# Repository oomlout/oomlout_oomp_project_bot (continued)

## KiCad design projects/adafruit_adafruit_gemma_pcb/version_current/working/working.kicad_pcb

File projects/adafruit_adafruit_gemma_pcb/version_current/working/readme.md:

# OOMP Project  
## Adafruit-Gemma-PCB  by adafruit  
  
oomp key: oomp_projects_flat_adafruit_adafruit_gemma_pcb  
(snippet of original readme)  
  
-- Adafruit Gemma Classic (ATtiny85) PCB  
<a href="http://www.adafruit.com/products/1222"><br/>  
Click here to purchase one from the Adafruit shop</a>  
  
Deprecation Warning: The Gemma bit-bang USB technique it uses doesn't work as well as it did in 2014, many modern computers won't work well. So while we still carry the Gemma so that people can maintain some older projects, we no longer recommend it. Please check out the Gemma M0. It has built-in USB, more capabilities, and is comparable in price!  
  
GEMMA is a tiny wearable platform board with a lot of might in a 1" diameter package. Powered by a Attiny85 and programmable with an Arduino IDE over USB, you'll be able to realize any wearable project!  
  
We wanted to design a microcontroller board that was small enough to fit into any project, and low cost enough to use without hesitation. Perfect for when you don't want to give up your Flora and you aren't willing to take apart the project you worked so hard to design. It's our lowest-cost sewable controller!  
  
The Attiny85 is a fun processor because despite being so small, it has 8K of flash, and 5 I/O pins, including analog inputs and PWM 'analog' outputs. We designed a USB bootloader so you can plug it into any computer and reprogram it over a USB port just like an Arduino (it uses 2 of the 5 I/O pins, leaving you with 3). In fact we even made some simple modifications to the Arduino IDE so that it works like a mini-Flora. Perfect   
  full source readme at [readme_src.md](readme_src.md)  
  
source repo at: [https://github.com/adafruit/Adafruit-Gemma-PCB](https://github.com/adafruit/Adafruit-Gemma-PCB)  
## Board  

## Schematic  

[schematic pdf](working_schematic.pdf)  
## Images

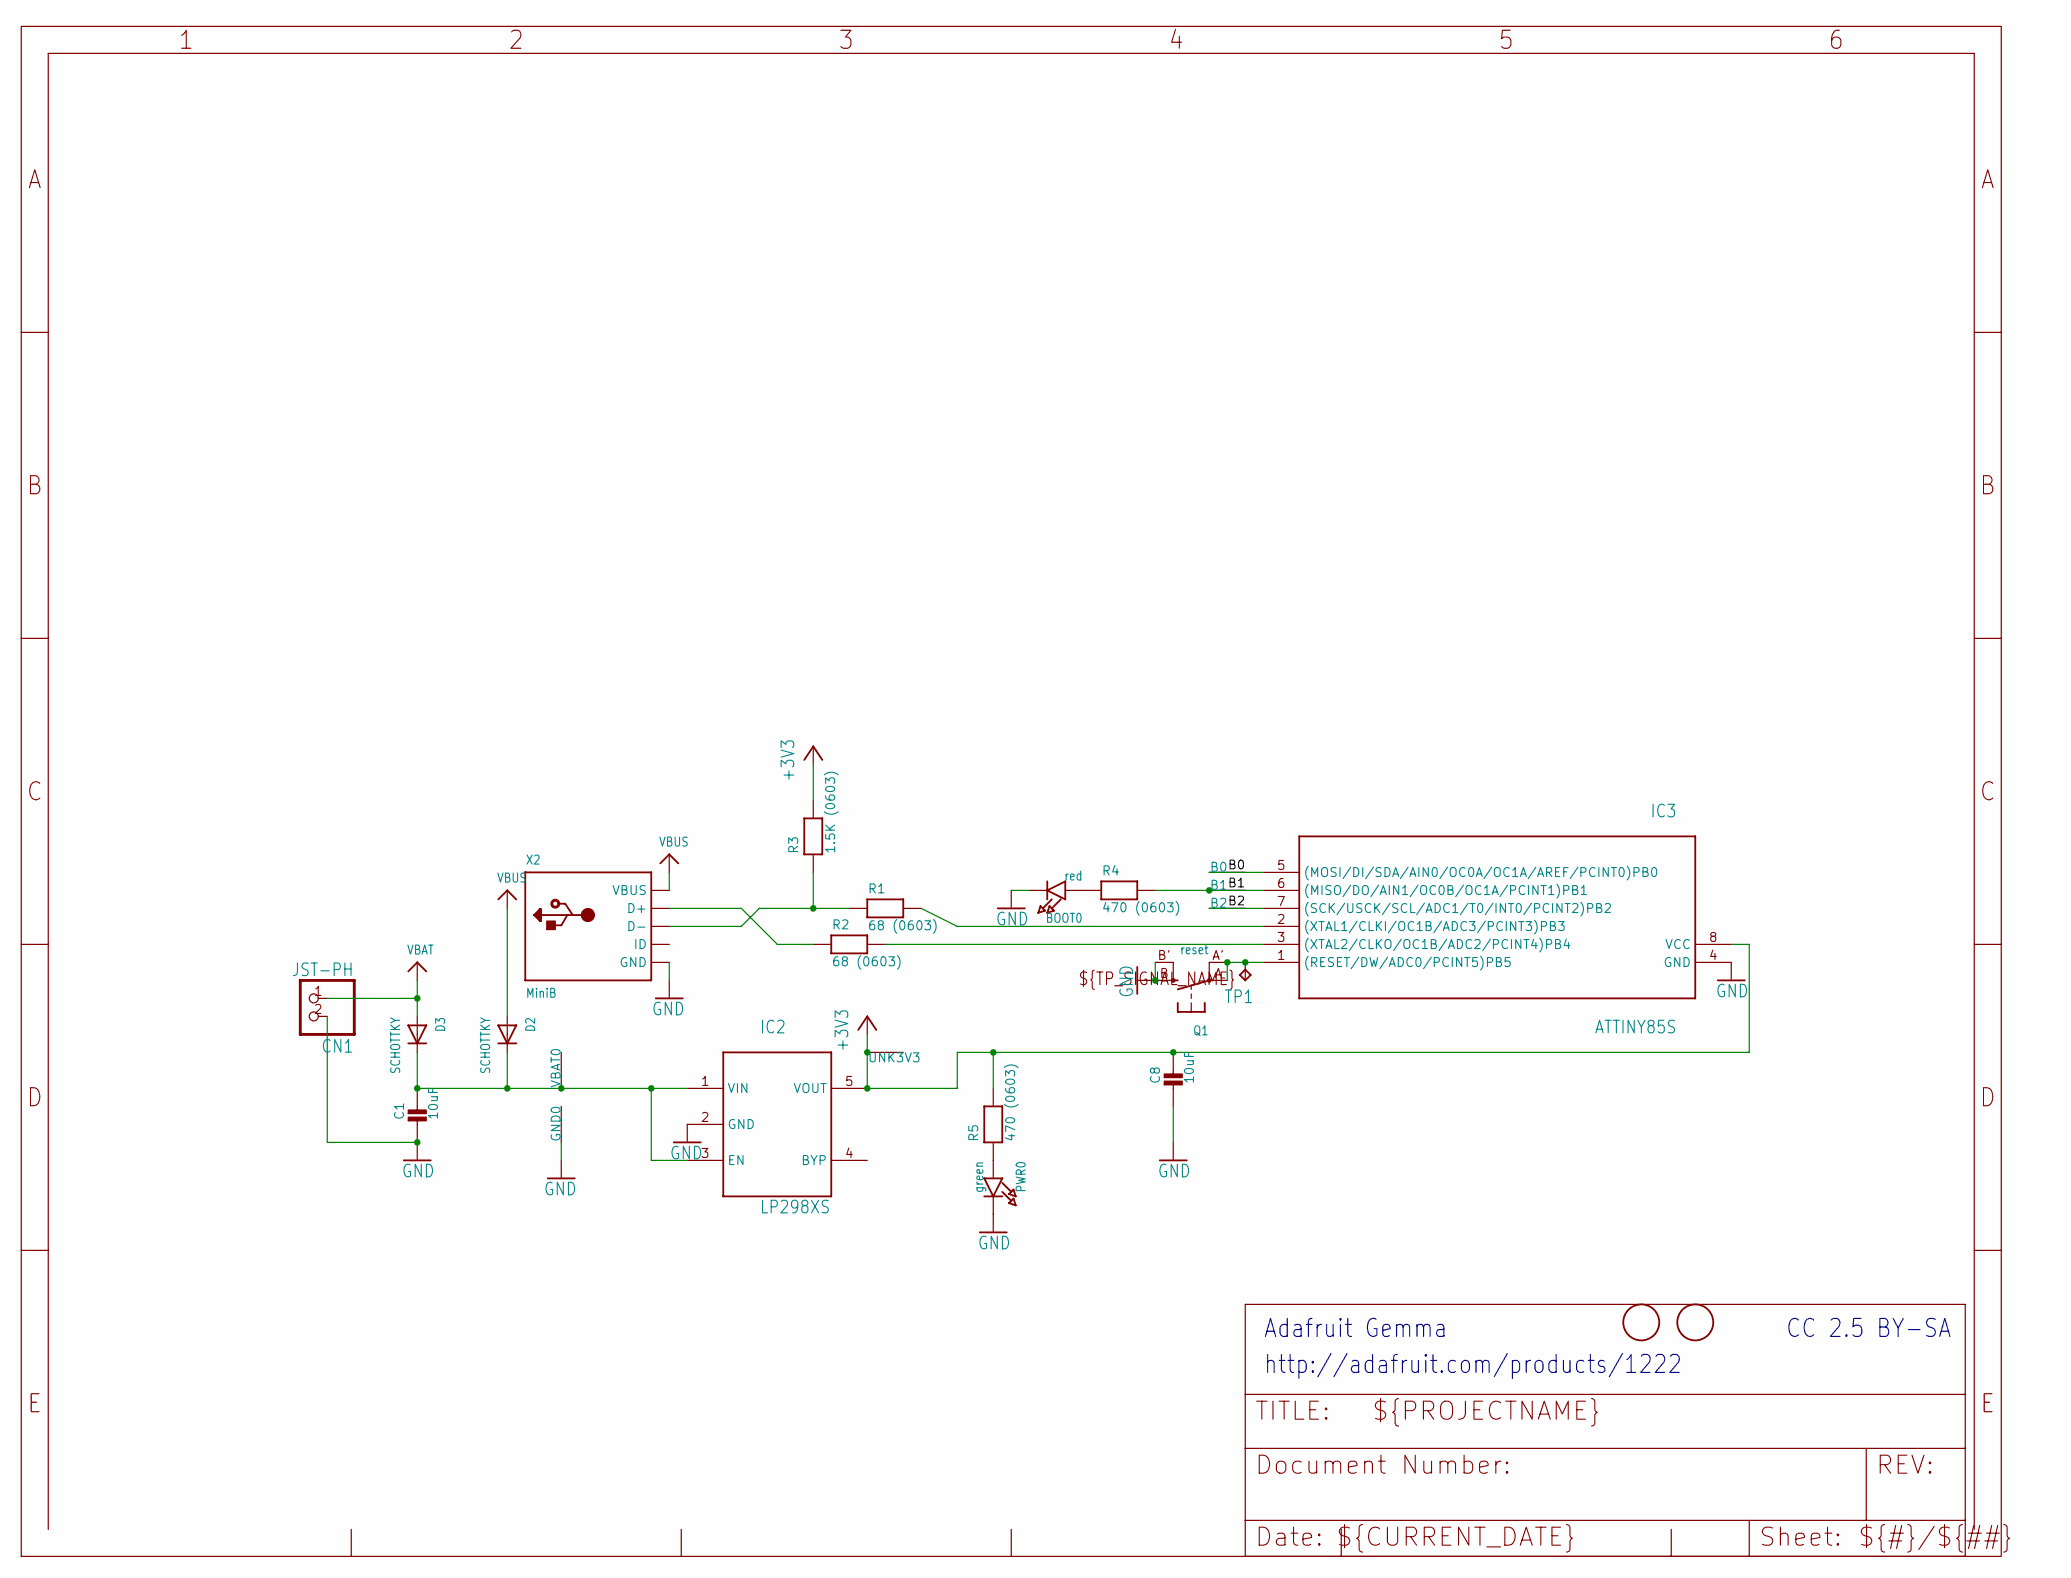
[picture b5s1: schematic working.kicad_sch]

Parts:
B0, B1, B2: SEWTAP-2.0IN; SEWINGTAP_2.0
BOOT0: red; CHIPLED_0805_NOOUTLINE
C1, C8: 10uF; 0805-NO
CN1: JST-PH; JST-PH-2-SMT-RA
D2, D3: SCHOTTKY; SOD-123FL
GND0: SEWTAP-2.0IN; SEWINGTAP_2.0
IC2: LP298XS; SOT23-5L
IC3: ATTINY85S; SOIC8
PWR0: green; CHIPLED_0805_NOOUTLINE
Q1: reset; BTN_KMR2_4.6X2.8
R1, R2: 68 (0603); 0603-NO
R3: 1.5K (0603); 0603-NO
R4, R5: 470 (0603); 0603-NO
TP1: TPB2,54; B2,54
U$1, U$6: FIDUCIAL; FIDUCIAL_1MM
UNK3V3: SEWTAP-2.0IN; SEWINGTAP_2.0
VBAT0: SEWTAP-2.0IN; SEWINGTAP_2.0
X2: MiniB; USB-MINI_MEDIUM

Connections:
+3V3: C8.1, IC2.5 (VOUT), IC3.8 (VCC), R3.2, R5.2, UNK3V3.P$1
B0: B0.P$1, IC3.5 ((MOSI/DI/SDA/AIN0/OC0A/OC1A/AREF/PCINT0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)
B1: B1.P$1, IC3.6 ((MISO/DO/AIN1/OC0B/OC1A/PCINT1)PB1), R4.2
B2: B2.P$1, IC3.7 ((SCK/USCK/SCL/ADC1/T0/INT0/PCINT2)PB2)
GND: BOOT0.C, C1.2, C8.2, CN1.2 (1), GND0.P$1, IC2.2 (GND), IC3.4 (GND), PWR0.C, Q1.B (S), Q1.B' (S1), X2.GND, X2.GND1 (GND), X2.GND2 (GND), X2.GND3 (GND), X2.GND4 (GND)
unnamed: IC3.1 ((RESET/DW/ADC0/PCINT5)PB5), Q1.A, Q1.A' (P1), TP1.TP
unnamed: R2.1, X2.D+
unnamed: IC3.2 ((XTAL1/CLKI/OC1B/ADC3/PCINT3)PB3), R1.2
unnamed: IC3.3 ((XTAL2/CLKO/OC1B/ADC2/PCINT4)PB4), R2.2
unnamed: R1.1, R3.1, X2.D-
unnamed: BOOT0.A, R4.1
unnamed: C1.1, D2.C, D3.C, IC2.1 (VIN), IC2.3 (EN), VBAT0.P$1
unnamed: PWR0.A, R5.1
VBAT: CN1.1 (2), D3.A
VBUS: D2.A, X2.VBUS

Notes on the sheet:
CC 2.5 BY-SA
Adafruit Gemma
http://adafruit.com/products/1222

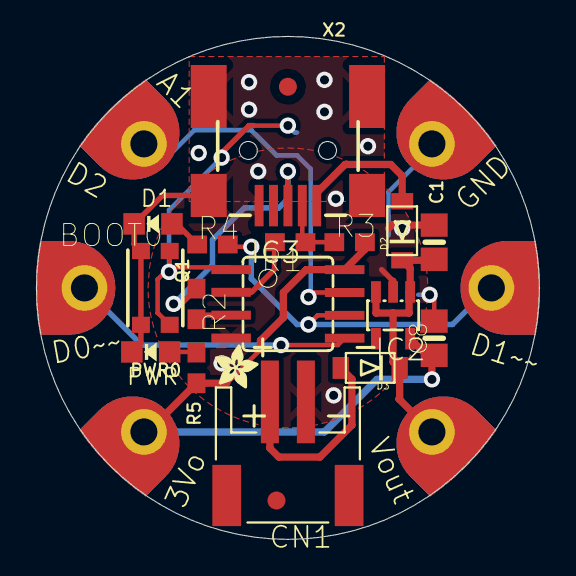
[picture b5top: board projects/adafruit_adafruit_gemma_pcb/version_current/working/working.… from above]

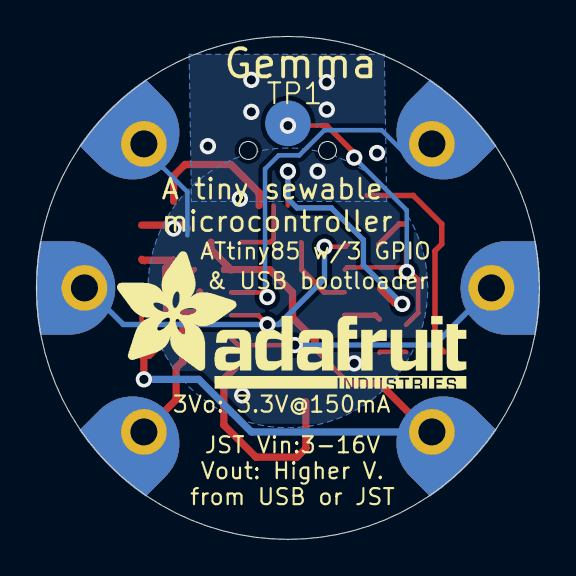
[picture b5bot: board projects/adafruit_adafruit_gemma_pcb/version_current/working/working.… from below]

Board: 16 copper layers, 27.9 x 27.9 mm, 27 parts (2 on the bottom side), 15 nets.

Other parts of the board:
U$2: ADAFRUIT_2.5MM
U$7: ADAFRUIT_TEXT_20MM

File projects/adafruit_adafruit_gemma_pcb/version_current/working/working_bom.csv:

Row,Description,Part,References,Value,Footprint,Quantity Per PCB,Status,Datasheet
1,,SEWTAP-2.0IN,B0 B1 B2 GND0 UNK3V3 VBAT0,SEWTAP-2.0IN,SEWINGTAP_2.0,6, ,
2,,LED0805_NOOUTLINE,BOOT0,red,CHIPLED_0805_NOOUTLINE,1, ,
3,,CAP_CERAMIC0805-NOOUTLINE,C1 C8,10uF,0805-NO,2, ,
4,,JST_2PIN-SMT-RA,CN1,JST-PH,JST-PH-2-SMT-RA,1, ,
5,,DIODE_SOD-123FL,D2 D3,SCHOTTKY,SOD-123FL,2, ,
6,,ATTINY85S,IC3,ATTINY85S,SOIC8,1, ,
7,,LP298XS,IC2,LP298XS,SOT23-5L,1, ,
8,,LED0805_NOOUTLINE,PWR0,green,CHIPLED_0805_NOOUTLINE,1, ,
9,,SWITCH_TACT_SMT4.6X2.8,Q1,reset,BTN_KMR2_4.6X2.8,1, ,
10,,RESISTOR_0603_NOOUT,R3,1.5K (0603),0603-NO,1, ,
11,,RESISTOR_0603_NOOUT,R4 R5,470 (0603),0603-NO,2, ,
12,,RESISTOR_0603_NOOUT,R1 R2,68 (0603),0603-NO,2, ,
13,,USB_MEDIUM,X2,MiniB,USB-MINI_MEDIUM,1, ,





Project info:
Schematic:,working
Variant:,default
Revision:,
Date:,2023-08-03_17-21-22
KiCad Version:,7.0.6-7.0.6~ubuntu22.04.1
Statistics:
Component Groups:,13
Component Count:,22 (0 SMD/ 0 THT)
Fitted Components:,22 (0 SMD/ 0 THT)
Number of PCBs:,1
Total Components:,22

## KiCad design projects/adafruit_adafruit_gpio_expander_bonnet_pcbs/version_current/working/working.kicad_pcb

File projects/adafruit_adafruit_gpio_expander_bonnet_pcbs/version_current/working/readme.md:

# OOMP Project  
## Adafruit-GPIO-Expander-Bonnet-PCBs  by adafruit  
  
oomp key: oomp_projects_flat_adafruit_adafruit_gpio_expander_bonnet_pcbs  
(snippet of original readme)  
  
-- Adafruit GPIO Expander Bonnet PCB  
  
<a href="http://www.adafruit.com/products/4132"><br/>  
Click here to purchase one from the Adafruit shop</a>  
  
PCB files for the Adafruit GPIO Expander Bonnet. Format is EagleCAD schematic and board layout  
* https://www.adafruit.com/product/4132  
  
--- Description  
  
The Raspberry Pi is an amazing single board computer - and one of the best parts is that GPIO connector! 40 pins of digital goodness you can twiddle to control LEDs, sensors, buttons, radios, displays - just about any device you can imagine. This Adafruit GPIO Expander Bonnet will give you even more digital deliciousness - 16 more digital input/output pins are yours for any desire you have. The outputs are grouped into two 16-pin connectors that have a matching ground pin. You can set each pin to be a digital output (high or low) or as an input, with an internal pull-up if you like!  
  
Simply pop the Bonnet on top of your Pi, the circuitry connects to the SDA/SCL I2C pins for control. The MCP23017 chip converts our Python commands to pin instructions.  
  
When used as an output, each pin can supply up to 20mA (current clamped) - so you can drive LEDs directly. The datasheet recommends you keep the total current draw to under 125mA for the whole chip. We set up the expander chip for 5V logic by default (the I2C is level shifted so that's 3V logic). We did that so you can drive white, blue or green LEDs that sometimes aren't too happy with  
  full source readme at [readme_src.md](readme_src.md)  
  
source repo at: [https://github.com/adafruit/Adafruit-GPIO-Expander-Bonnet-PCBs](https://github.com/adafruit/Adafruit-GPIO-Expander-Bonnet-PCBs)  
## Board  

## Schematic  

[schematic pdf](working_schematic.pdf)  
## Images

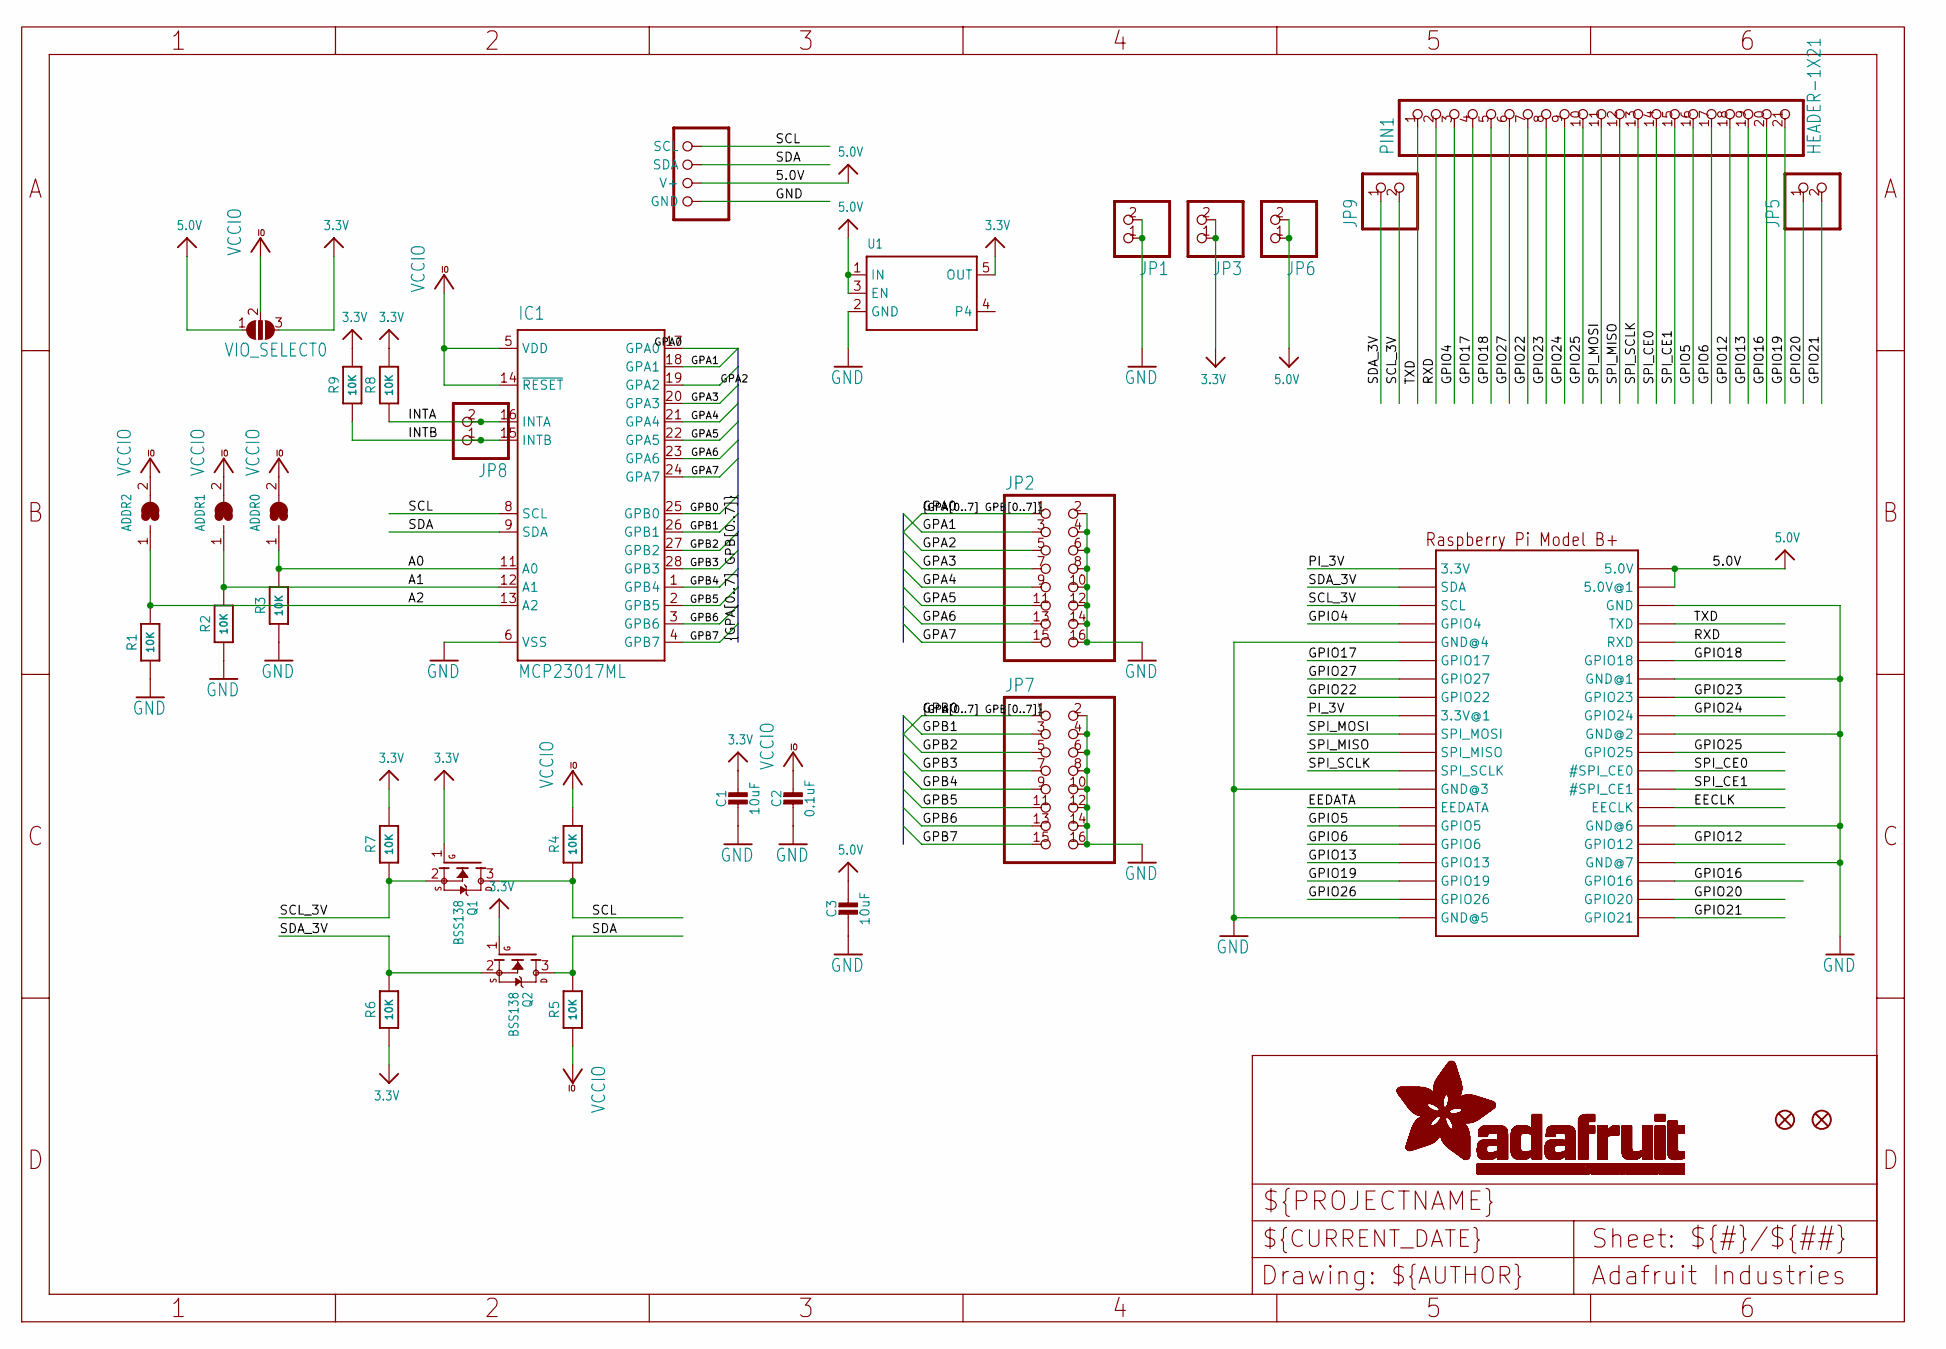
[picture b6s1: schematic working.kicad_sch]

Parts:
ADDR0, ADDR1, ADDR2: SOLDERJUMPER; SOLDERJUMPER_ARROW_NOPASTE
C1, C3: 10uF; 0805-NO
C2: 0.1uF; 0603-NO
FID1, FID2: FIDUCIAL_1MM
IC1: MCP23017ML; QFN28-ML_6X6MM
JP1, JP3, JP5, JP6, JP8, JP9: HEADER-1X2ROUND; 1X02_ROUND
JP2, JP7: HEADER-2X8_SHROUDED; 2X08_SHROUDED
PIN1: HEADER-1X21; 1X21_ROUND_70MIL
Q1, Q2: BSS138; SOT23-WIDE
R1, R2, R3, R4, R5, R6, R7, R8, R9: 10K; 0603-NO
RPI2: PIBONNET_STEMMA_2STEMMA_SMTTHM; PI_BONNET_2STEMMA_SMT
U1: VREG_SOT23-5; SOT23-5
VIO_SELECT0: SOLDERJUMPER_2WAY; SOLDERJUMPER_2WAY_OPEN_NOPASTE

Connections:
3.3V: C1.1, JP3.1, JP3.2, Q1.1 (G), Q2.1 (G), R6.1, R7.2, R8.2, R9.2, U1.5 (OUT), VIO_SELECT0.3
5.0V: C3.1, JP6.1, JP6.2, RPI2.2 (5.0V), RPI2.4 (5.0V@1), RPI2.S2 (5.0V), RPI2.S4 (5.0V@1), RPI2.V+, RPI2.V+1 (V+), U1.1 (IN), U1.3 (EN), VIO_SELECT0.1
A0: ADDR0.1, IC1.11 (A0), R3.2
A1: ADDR1.1, IC1.12 (A1), R2.2
A2: ADDR2.1, IC1.13 (A2), R1.2
EECLK: RPI2.28 (EECLK), RPI2.S28 (EECLK)
EEDATA: RPI2.27 (EEDATA), RPI2.S27 (EEDATA)
GND: C1.2, C2.2, C3.2, IC1.6 (VSS), JP1.1, JP1.2, JP2.2, JP2.4, JP2.6, JP2.8, JP2.10, JP2.12, JP2.14, JP2.16, JP7.2, JP7.4, JP7.6, JP7.8, JP7.10, JP7.12, JP7.14, JP7.16, R1.1, R2.1, R3.1, RPI2.6 (GND), RPI2.9 (GND@4), RPI2.14 (GND@1), RPI2.20 (GND@2), RPI2.25 (GND@3), RPI2.30 (GND@6), RPI2.34 (GND@7), RPI2.39 (GND@5), RPI2.GND, RPI2.GND1 (GND), RPI2.S6 (GND), RPI2.S9 (GND@4), RPI2.S14 (GND@1), RPI2.S20 (GND@2), RPI2.S25 (GND@3), RPI2.S30 (GND@6), RPI2.S34 (GND@7), RPI2.S39 (GND@5), U1.2 (GND)
GPA1: IC1.18 (GPA1), JP2.3
GPA2: IC1.19 (GPA2), JP2.5
GPA3: IC1.20 (GPA3), JP2.7
GPA4: IC1.21 (GPA4), JP2.9
GPA5: IC1.22 (GPA5), JP2.11
GPA6: IC1.23 (GPA6), JP2.13
GPA7: IC1.24 (GPA7), JP2.15
GPB1: IC1.26 (GPB1), JP7.3
GPB2: IC1.27 (GPB2), JP7.5
GPB3: IC1.28 (GPB3), JP7.7
GPB4: IC1.1 (GPB4), JP7.9
GPB5: IC1.2 (GPB5), JP7.11
GPB6: IC1.3 (GPB6), JP7.13
GPB7: IC1.4 (GPB7), JP7.15
GPIO4: PIN1.3, RPI2.7 (GPIO4), RPI2.S7 (GPIO4)
GPIO5: PIN1.16, RPI2.29 (GPIO5), RPI2.S29 (GPIO5)
GPIO6: PIN1.17, RPI2.31 (GPIO6), RPI2.S31 (GPIO6)
GPIO12: PIN1.18, RPI2.32 (GPIO12), RPI2.S32 (GPIO12)
GPIO13: PIN1.19, RPI2.33 (GPIO13), RPI2.S33 (GPIO13)
GPIO16: PIN1.20, RPI2.36 (GPIO16), RPI2.S36 (GPIO16)
GPIO17: PIN1.4, RPI2.11 (GPIO17), RPI2.S11 (GPIO17)
GPIO18: PIN1.5, RPI2.12 (GPIO18), RPI2.S12 (GPIO18)
GPIO19: PIN1.21, RPI2.35 (GPIO19), RPI2.S35 (GPIO19)
GPIO20: JP5.1, RPI2.38 (GPIO20), RPI2.S38 (GPIO20)
GPIO21: JP5.2, RPI2.40 (GPIO21), RPI2.S40 (GPIO21)
GPIO22: PIN1.7, RPI2.15 (GPIO22), RPI2.S15 (GPIO22)
GPIO23: PIN1.8, RPI2.16 (GPIO23), RPI2.S16 (GPIO23)
GPIO24: PIN1.9, RPI2.18 (GPIO24), RPI2.S18 (GPIO24)
GPIO25: PIN1.10, RPI2.22 (GPIO25), RPI2.S22 (GPIO25)
GPIO26: RPI2.37 (GPIO26), RPI2.S37 (GPIO26)
GPIO27: PIN1.6, RPI2.13 (GPIO27), RPI2.S13 (GPIO27)
INTA: IC1.16 (INTA), JP8.2, R8.1
INTB: IC1.15 (INTB), JP8.1, R9.1
PI_3V: RPI2.1 (3.3V), RPI2.17 (3.3V@1), RPI2.S1 (3.3V), RPI2.S17 (3.3V@1)
RXD: PIN1.2, RPI2.10 (RXD), RPI2.S10 (RXD)
SCL: IC1.8 (SCL), Q1.3 (D), R4.1, RPI2.SCL, RPI2.SCL1 (SCL)
SCL_3V: JP9.2, Q1.2 (S), R7.1, RPI2.5 (SCL), RPI2.S5 (SCL)
SDA: IC1.9 (SDA), Q2.3 (D), R5.2, RPI2.SDA, RPI2.SDA1 (SDA)
SDA_3V: JP9.1, Q2.2 (S), R6.2, RPI2.3 (SDA), RPI2.S3 (SDA)
SPI_CE0: PIN1.14, RPI2.24 (#SPI_CE0), RPI2.S24 (#SPI_CE0)
SPI_CE1: PIN1.15, RPI2.26 (#SPI_CE1), RPI2.S26 (#SPI_CE1)
SPI_MISO: PIN1.12, RPI2.21 (SPI_MISO), RPI2.S21 (SPI_MISO)
SPI_MOSI: PIN1.11, RPI2.19 (SPI_MOSI), RPI2.S19 (SPI_MOSI)
SPI_SCLK: PIN1.13, RPI2.23 (SPI_SCLK), RPI2.S23 (SPI_SCLK)
TXD: PIN1.1, RPI2.8 (TXD), RPI2.S8 (TXD)
VCCIO: ADDR0.2, ADDR1.2, ADDR2.2, C2.1, IC1.5 (VDD), IC1.14 (~RESET), R4.2, R5.1, VIO_SELECT0.2

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
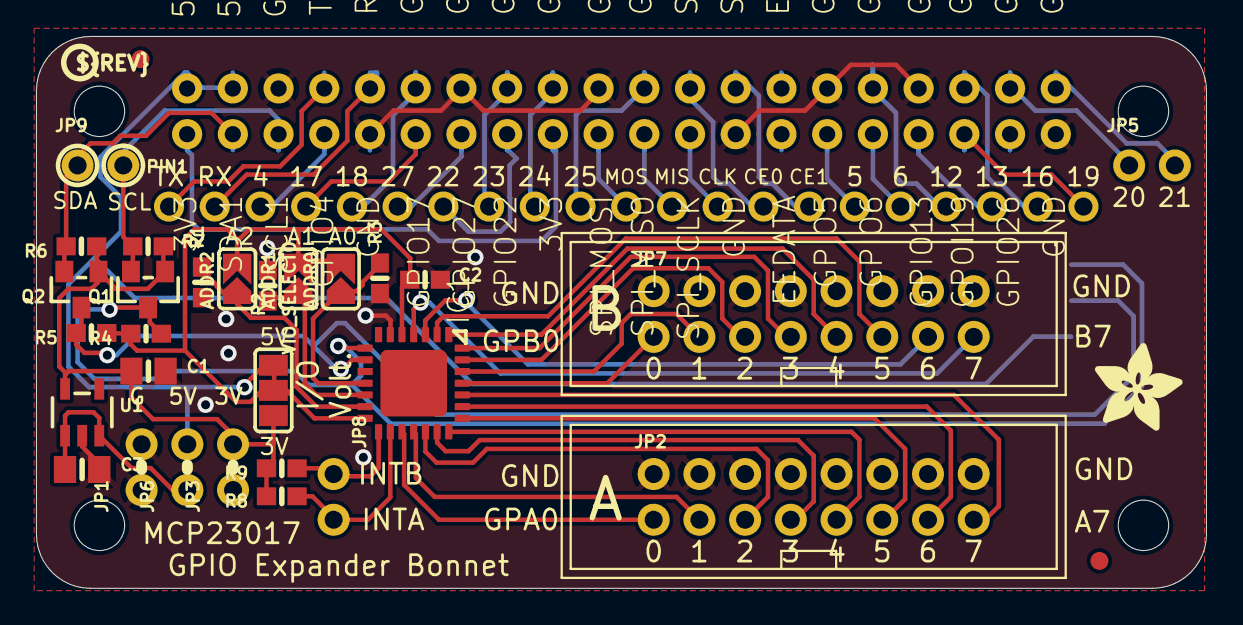
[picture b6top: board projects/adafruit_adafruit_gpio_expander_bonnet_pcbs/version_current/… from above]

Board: 2 copper layers, 65.0 x 30.7 mm, 34 parts (0 on the bottom side), 56 nets.

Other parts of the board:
U$12: ADAFRUIT_5MM
U$13: PCBFEAT-REV-040

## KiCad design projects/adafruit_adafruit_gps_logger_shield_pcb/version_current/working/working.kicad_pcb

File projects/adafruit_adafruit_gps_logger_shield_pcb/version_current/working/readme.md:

# Adafruit-GPS-Logger-Shield-PCB by adafruit  
This is a harvested standardized copy of a project from github.  
The original project can be found at:  
https://github.com/adafruit/Adafruit-GPS-Logger-Shield-PCB  
Please consult that link for additional, details, files, and license information.  
Note: It was auto harvested and if the original repo had more than one board file or anything out of the ordinary the files here are likely not representative.

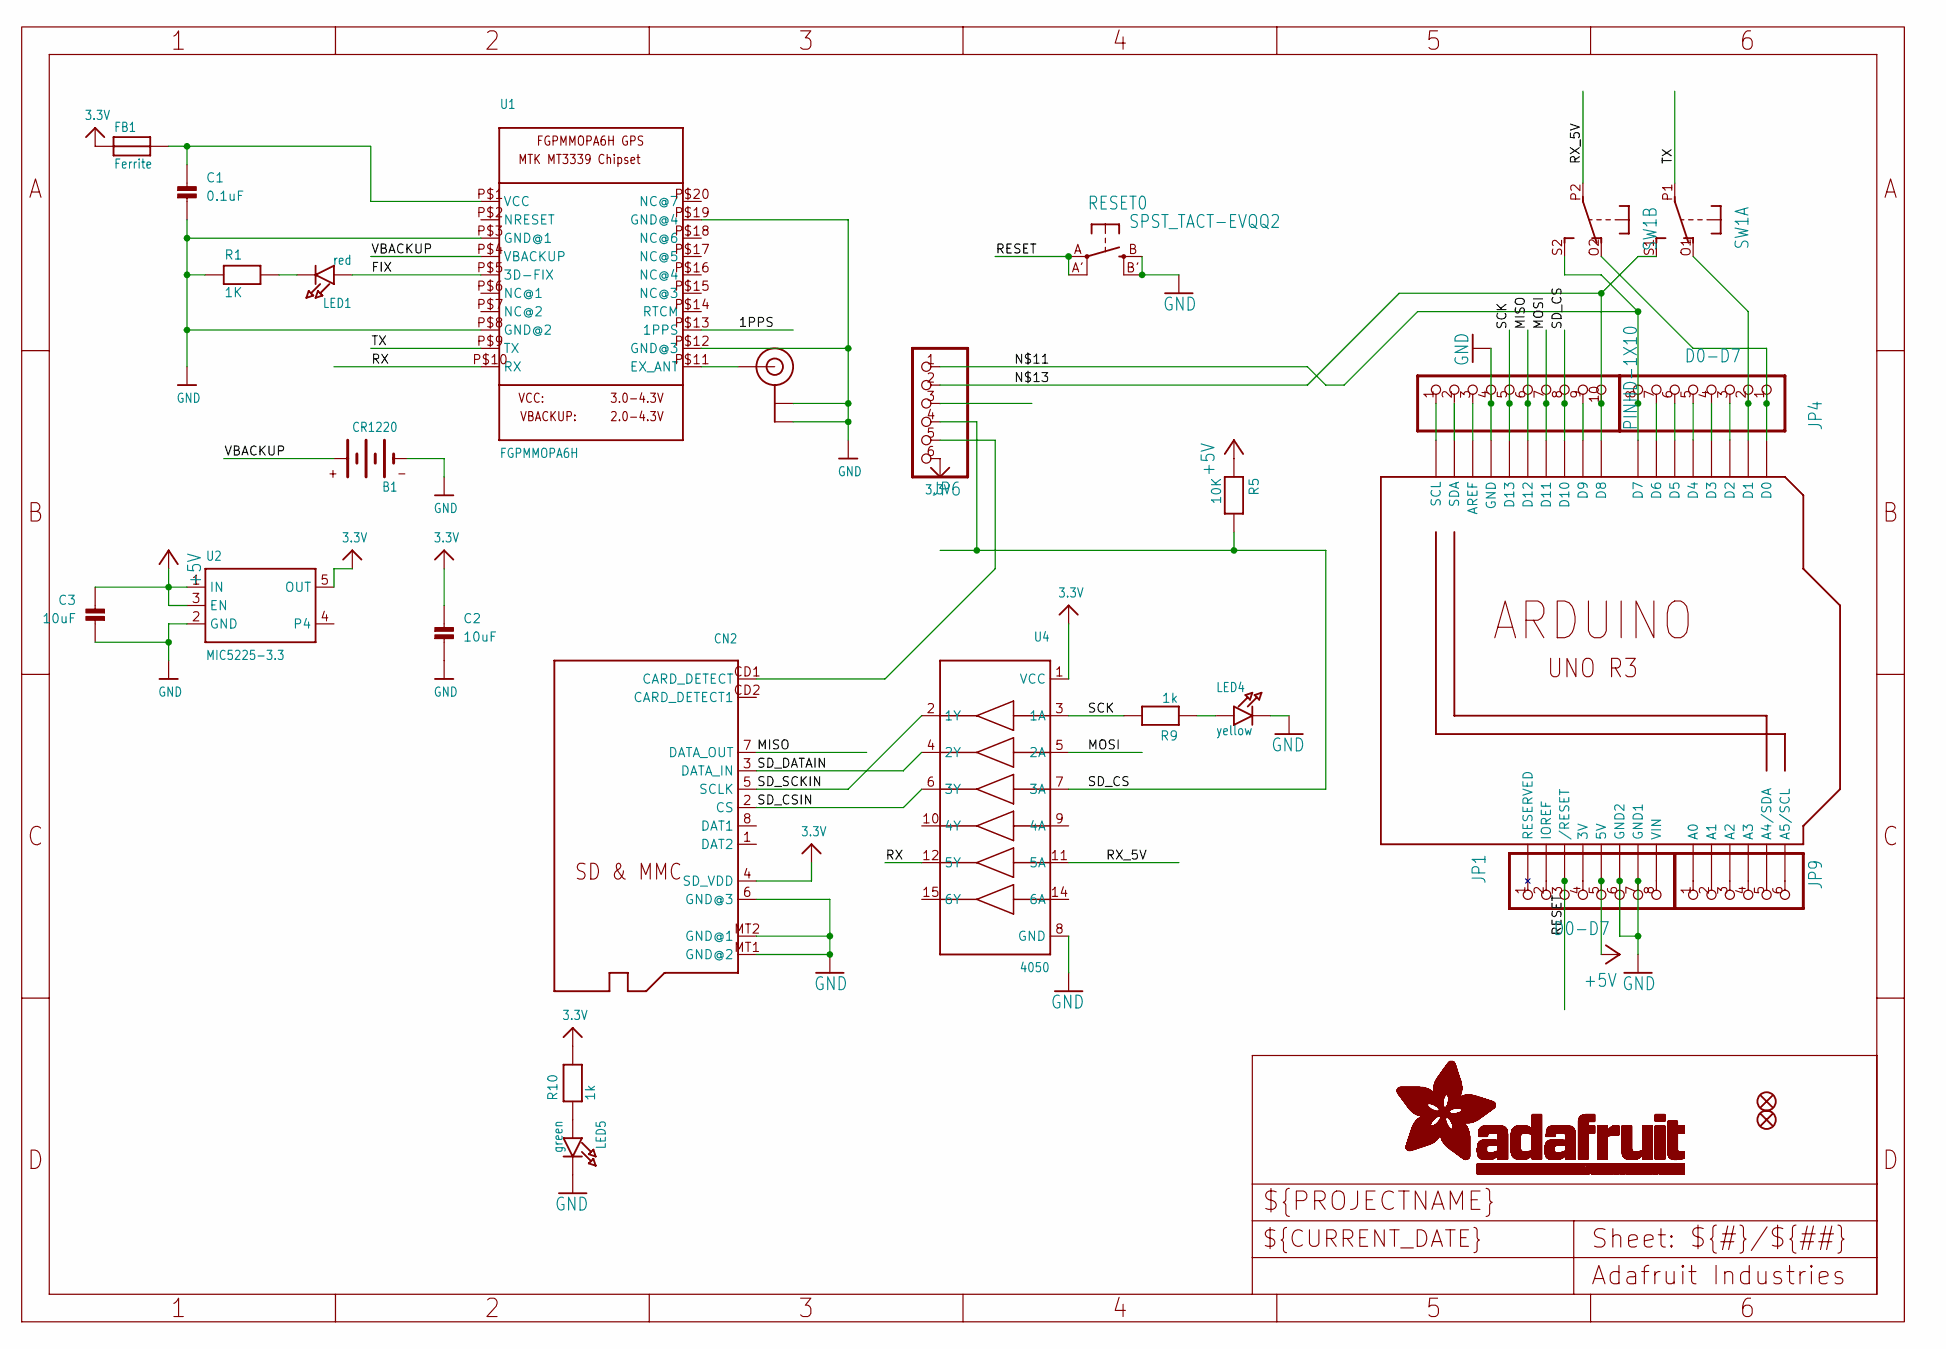
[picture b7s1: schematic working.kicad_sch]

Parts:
B1: CR1220
C1: 0.1uF; 0805@1
C2, C3: 10uF; 0805@1
CN2: MICROSD
FB1: Ferrite; 0805@1
FID1, FID2: FIDUCIAL""; FIDUCIAL_1MM
JP1, JP4: D0-D7; 1X08-BIG
JP6, JP9: PINHD-1X6B; 1X06-BIG
LED1: red; CHIPLED_0805
LED4: yellow; CHIPLED_0805
LED5: green; CHIPLED_0805
R1: 1K; 0805
R5: 10K; 0805
R9, R10: 1k; 0805
RESET0: SPST_TACT-EVQQ2; EVQ-Q2
SW1: DPDT-EG1390; EG1390
U1: FGPMMOPA6H
U2: MIC5225-3.3; SOT23-5
U3: ARDUINOR3-DIMENSION; ARDUINOR3
U4: 4050; SOIC16
U$9: PINHD-1X10; 1X10-BIG
U$20: U.FL

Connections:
1PPS: JP6.3, U1.P$13 (1PPS)
3.3V: C2.1, CN2.4 (SD_VDD), FB1.1, JP6.6, R10.2, U2.5 (OUT), U4.1 (VCC)
+5V: C3.1, JP1.5, R5.1, U2.1 (IN), U2.3 (EN), U3.5V
FIX: LED1.A, U1.P$5 (3D-FIX)
GND: B1.-, C1.2, C2.2, C3.2, CN2.6 (GND@3), CN2.MT1 (GND@2), CN2.MT2 (GND@1), JP1.6, JP1.7, LED4.C, LED5.C, R1.1, RESET0.B (S), RESET0.B' (S1), U1.P$3 (GND@1), U1.P$8 (GND@2), U1.P$12 (GND@3), U1.P$19 (GND@4), U2.2 (GND), U3.GND, U3.GND1, U3.GND2, U4.8 (GND), U$9.4, U$20.P$1 (GND@0), U$20.P$2 (GND@1)
MISO: CN2.7 (DATA_OUT), U3.D12, U$9.6
MOSI: U3.D11, U4.5 (2A), U$9.7
unnamed: C1.1, FB1.2, U1.P$1 (VCC)
unnamed: LED1.C, R1.2
unnamed: JP1.1, U3.RESERVED
unnamed: U1.P$11 (EX_ANT), U$20.P$3 (SIGNAL)
unnamed: JP1.2, U3.IOREF
unnamed: JP1.4, U3.3V
unnamed: U3.SCL, U$9.1
unnamed: LED4.A, R9.1
unnamed: JP9.6, U3.A5 (A5/SCL)
unnamed: JP9.5, U3.A4 (A4/SDA)
unnamed: JP4.8, JP6.1, SW1.S2 (S), U3.D7
unnamed: U3.SDA, U$9.2
unnamed: JP6.2, SW1.S1 (S), U3.D8, U$9.10
unnamed: JP4.2, SW1.O1 (O), U3.D1
unnamed: JP1.8, U3.VIN
unnamed: JP4.3, U3.D2
unnamed: JP4.4, U3.D3
unnamed: JP4.5, U3.D4
unnamed: JP4.6, U3.D5
unnamed: JP4.7, U3.D6
unnamed: U3.AREF, U$9.3
unnamed: U3.D9, U$9.9
unnamed: LED5.A, R10.1
unnamed: JP9.1, U3.A0
unnamed: JP9.2, U3.A1
unnamed: JP9.3, U3.A2
unnamed: JP9.4, U3.A3
unnamed: JP4.1, SW1.O2 (O), U3.D0
RESET: JP1.3, RESET0.A, RESET0.A' (P1), U3.RESET (/RESET)
RX: U1.P$10 (RX), U4.12 (5Y)
RX_5V: SW1.P2, U4.11 (5A)
SCK: R9.2, U3.D13, U4.3 (1A), U$9.5
SD_CD: CN2.CD1 (CARD_DETECT), JP6.5
SD_CS: JP6.4, R5.2, U3.D10, U4.7 (3A), U$9.8
SD_CSIN: CN2.2 (CS), U4.6 (3Y)
SD_DATAIN: CN2.3 (DATA_IN), U4.4 (2Y)
SD_SCKIN: CN2.5 (SCLK), U4.2 (1Y)
TX: SW1.P1, U1.P$9 (TX)
VBACKUP: B1.+$1 (+), U1.P$4 (VBACKUP)

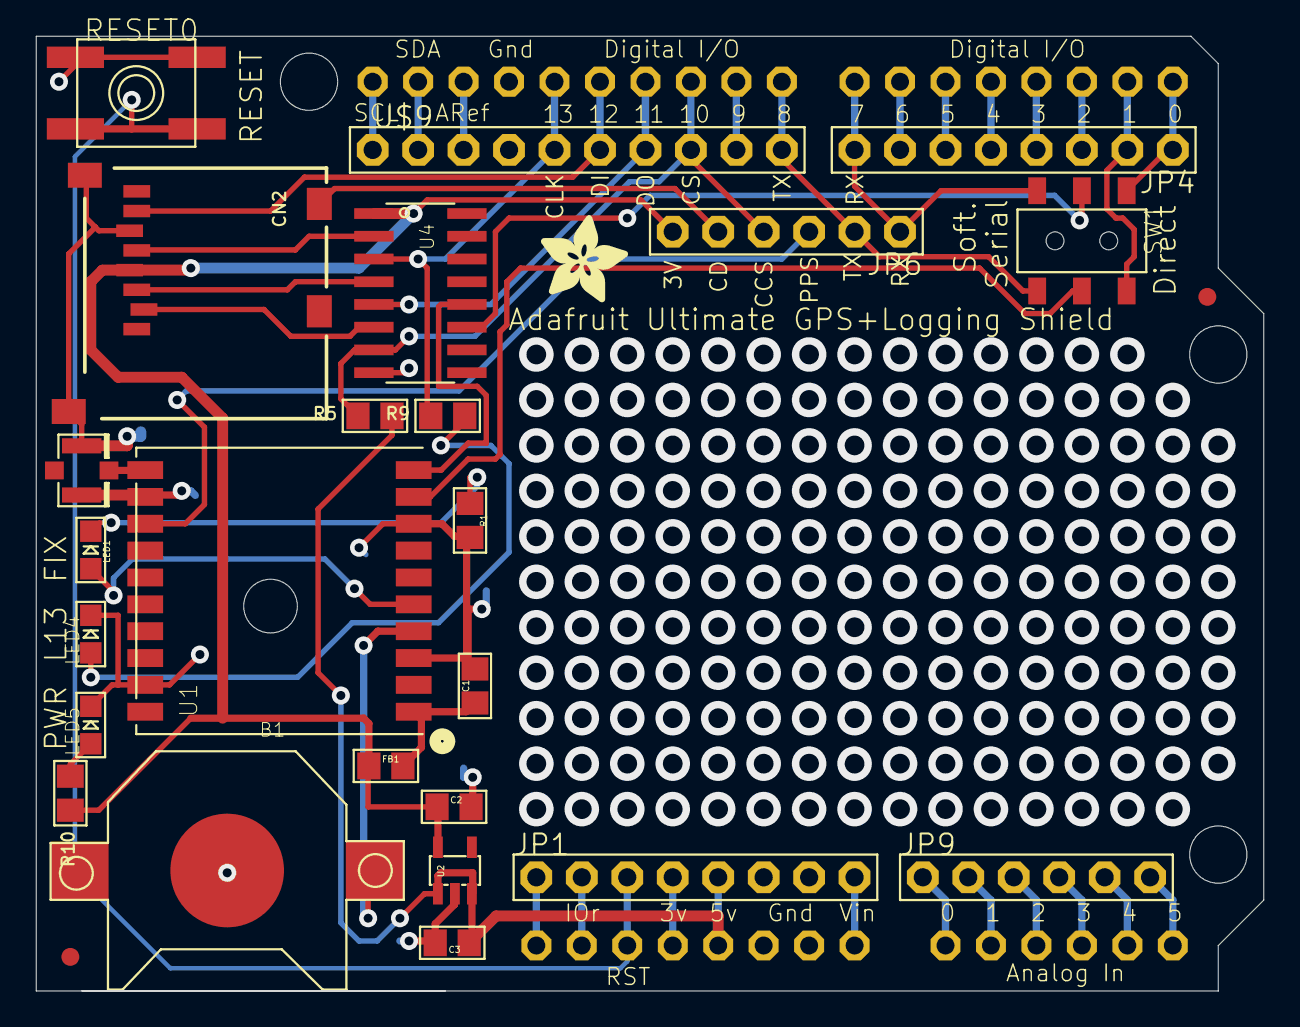
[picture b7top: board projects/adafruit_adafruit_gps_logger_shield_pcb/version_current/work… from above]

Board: 2 copper layers, 68.6 x 53.3 mm, 32 parts (1 on the bottom side), 46 nets.

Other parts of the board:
@HOLE0, @HOLE1, @HOLE2: (no value)
U$13: ADAFRUIT_5MM
U$15: ADAFRUIT_TEXT_30MM
